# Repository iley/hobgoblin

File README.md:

# Hobgoblin: Z80-based single-board computer

## Specs

 - Z80 CPU running at 10MHz
 - 64 KiB RAM
 - 8 x 16 KiB ROM. ROM bank is selectable with a DIP switch
 - ROM can be paged out for CP/M compatibility
 - Built-in usb-to-serial adapter for convenience of use with modern computers
 - 2 RC2014-compatible extension slots.

## Memory map

```
 FFFF ┌─────────┐
      │         │
      │         │
      │         │
      │         │
      │   RAM   │
      │         │
      │         │
      │         │
 4000 ├─────────┤
      │         │
      │   ROM   │
      │         │
 0000 └─────────┘
```

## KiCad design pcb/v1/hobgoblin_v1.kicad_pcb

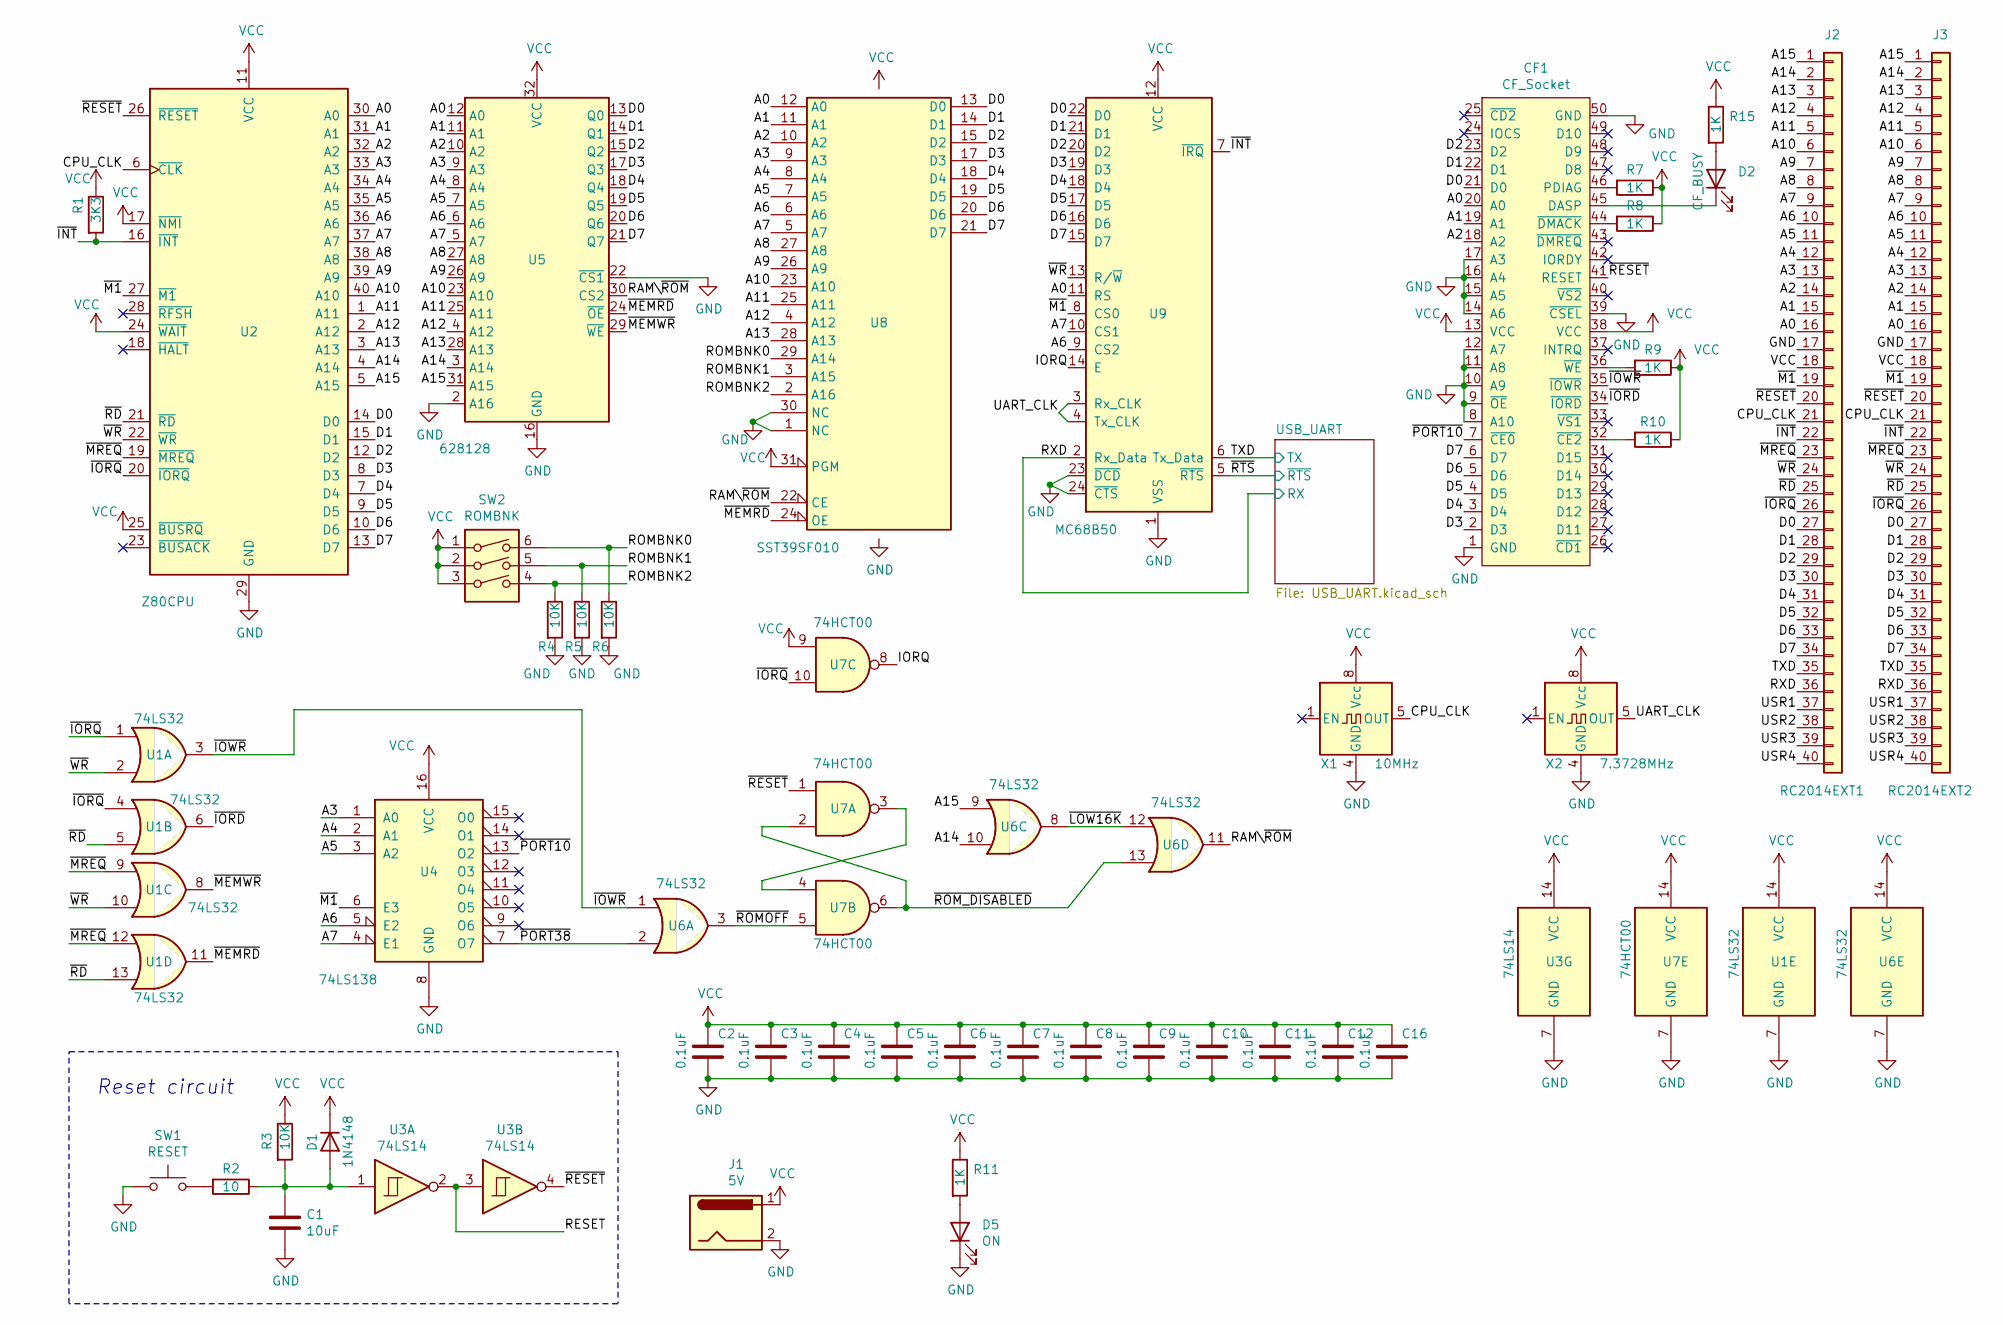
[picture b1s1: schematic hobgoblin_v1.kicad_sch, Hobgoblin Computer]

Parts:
C1: 10uF; CP_Radial_D4.0mm_P1.50mm
C2, C3, C4, C5, C6, C7, C8, C9, C10, C11, C12, C16: 0.1uF; C_Disc_D3.8mm_W2.6mm_P2.50mm
CF1: CF_Socket; CF-Card_3M_N7E507516PK20
D1: 1N4148; D_DO-35_SOD27_P7.62mm_Horizontal
D2: CF_BUSY; LED_D3.0mm
D5: ON; LED_D3.0mm
J1: 5V; BarrelJack_Horizontal
J2: RC2014EXT1; RC2014_Connector
J3: RC2014EXT2; RC2014_Connector
R1: 3K3; R_Axial_DIN0207_L6.3mm_D2.5mm_P10.16mm_Horizontal
R2: 10; R_Axial_DIN0207_L6.3mm_D2.5mm_P10.16mm_Horizontal
R3, R4, R5, R6: 10K; R_Axial_DIN0207_L6.3mm_D2.5mm_P10.16mm_Horizontal
R7, R8, R9, R10, R11, R15: 1K; R_Axial_DIN0207_L6.3mm_D2.5mm_P10.16mm_Horizontal
SW1: RESET; SW_PUSH_6mm
SW2: ROMBNK; SW_DIP_SPSTx03_Slide_6.7x9.18mm_W7.62mm_P2.54mm_LowProfile
U1, U6: 74LS32; DIP-14_W7.62mm_LongPads
U2: Z80CPU; DIP-40_W15.24mm_LongPads
U3: 74LS14; DIP-14_W7.62mm_LongPads
U4: 74LS138; DIP-16_W7.62mm_LongPads
U5: 628128; DIP-32_W15.24mm_LongPads
U7: 74HCT00; DIP-14_W7.62mm_LongPads
U8: SST39SF010; DIP-32_W15.24mm_LongPads
U9: MC68B50; DIP-24_W15.24mm_LongPads
X1: 10MHz; Oscillator_DIP-8
X2: 7.3728MHz; Oscillator_DIP-8

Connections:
/A0: CF1.20 (A0), J2.16, J3.16, U2.30 (A0), U5.12 (A0), U8.12 (A0), U9.11 (RS)
/A1: CF1.19 (A1), J2.15, J3.15, U2.31 (A1), U5.11 (A1), U8.11 (A1)
/A2: CF1.18 (A2), J2.14, J3.14, U2.32 (A2), U5.10 (A2), U8.10 (A2)
/A3: J2.13, J3.13, U2.33 (A3), U4.1 (A0), U5.9 (A3), U8.9 (A3)
/A4: J2.12, J3.12, U2.34 (A4), U4.2 (A1), U5.8 (A4), U8.8 (A4)
/A5: J2.11, J3.11, U2.35 (A5), U4.3 (A2), U5.7 (A5), U8.7 (A5)
/A6: J2.10, J3.10, U2.36 (A6), U4.5 (E2), U5.6 (A6), U8.6 (A6), U9.9 (CS2)
/A7: J2.9, J3.9, U2.37 (A7), U4.4 (E1), U5.5 (A7), U8.5 (A7), U9.10 (CS1)
/A8: J2.8, J3.8, U2.38 (A8), U5.27 (A8), U8.27 (A8)
/A9: J2.7, J3.7, U2.39 (A9), U5.26 (A9), U8.26 (A9)
/A10: J2.6, J3.6, U2.40 (A10), U5.23 (A10), U8.23 (A10)
/A11: J2.5, J3.5, U2.1 (A11), U5.25 (A11), U8.25 (A11)
/A12: J2.4, J3.4, U2.2 (A12), U5.4 (A12), U8.4 (A12)
/A13: J2.3, J3.3, U2.3 (A13), U5.28 (A13), U8.28 (A13)
/A14: J2.2, J3.2, U2.4 (A14), U5.3 (A14), U6.10
/A15: J2.1, J3.1, U2.5 (A15), U5.31 (A15), U6.9
/CPU_CLK: J2.21, J3.21, U2.6 (~CLK), X1.5 (OUT)
/D0: CF1.21 (D0), J2.27, J3.27, U2.14 (D0), U5.13 (Q0), U8.13 (D0), U9.22 (D0)
/D1: CF1.22 (D1), J2.28, J3.28, U2.15 (D1), U5.14 (Q1), U8.14 (D1), U9.21 (D1)
/D2: CF1.23 (D2), J2.29, J3.29, U2.12 (D2), U5.15 (Q2), U8.15 (D2), U9.20 (D2)
/D3: CF1.2 (D3), J2.30, J3.30, U2.8 (D3), U5.17 (Q3), U8.17 (D3), U9.19 (D3)
/D4: CF1.3 (D4), J2.31, J3.31, U2.7 (D4), U5.18 (Q4), U8.18 (D4), U9.18 (D4)
/D5: CF1.4 (D5), J2.32, J3.32, U2.9 (D5), U5.19 (Q5), U8.19 (D5), U9.17 (D5)
/D6: CF1.5 (D6), J2.33, J3.33, U2.10 (D6), U5.20 (Q6), U8.20 (D6), U9.16 (D6)
/D7: CF1.6 (D7), J2.34, J3.34, U2.13 (D7), U5.21 (Q7), U8.21 (D7), U9.15 (D7)
/IORQ: U7.8, U9.14 (E)
/RAM\~ROM: U5.30 (CS2), U6.11, U8.22 (CE)
/RESET: U3.2, U3.3
/ROMBNK0: R6.1, SW2.6, U8.29 (A14)
/ROMBNK1: R5.1, SW2.5, U8.3 (A15)
/ROMBNK2: R4.1, SW2.4, U8.2 (A16)
/RXD: J2.36, J3.36, U9.2 (Rx_Data); also elsewhere on the board
/TXD: J2.35, J3.35, U9.6 (Tx_Data); also elsewhere on the board
/UART_CLK: U9.3 (Rx_CLK), U9.4 (Tx_CLK), X2.5 (OUT)
/USR1: J2.37, J3.37
/USR2: J2.38, J3.38
/USR3: J2.39, J3.39
/USR4: J2.40, J3.40
/~INT: J2.22, J3.22, R1.2, U2.16 (~INT), U9.7 (~IRQ)
/~IORD: CF1.34 (~IORD), U1.6
/~IORQ: J2.26, J3.26, U1.1, U1.4, U2.20 (~IORQ), U7.10
/~IOWR: CF1.35 (~IOWR), U1.3, U6.1
/~LOW16K: U6.8, U6.12
/~M1: J2.19, J3.19, U2.27 (~M1), U4.6 (E3), U9.8 (CS0)
/~MEMRD: U1.11, U5.24 (~OE), U8.24 (OE)
/~MEMWR: U1.8, U5.29 (~WE)
/~MREQ: J2.23, J3.23, U1.9, U1.12, U2.19 (~MREQ)
/~PORT10: CF1.7 (~CE0), U4.13 (O2)
/~PORT38: U4.7 (O7), U6.2
/~RD: J2.25, J3.25, U1.5, U1.13, U2.21 (~RD)
/~RESET: CF1.41 (RESET), J2.20, J3.20, U2.26 (~RESET), U3.4, U7.1
/~ROMOFF: U6.3, U7.5
/~ROM_DISABLED: U6.13, U7.2, U7.6
/~RTS: U9.5 (~RTS); also elsewhere on the board
/~WR: J2.24, J3.24, U1.2, U1.10, U2.22 (~WR), U9.13 (R/~W)
GND: C1.2, C2.2, C3.2, C4.2, C5.2, C6.2, C7.2, C8.2, C9.2, C10.2, C11.2, C12.2, C16.2, CF1.1 (GND), CF1.8 (A10), CF1.9 (~OE), CF1.10 (A9), CF1.11 (A8), CF1.12 (A7), CF1.14 (A6), CF1.15 (A5), CF1.16 (A4), CF1.17 (A3), CF1.39 (~CSEL), CF1.50 (GND), D5.1 (K), J1.2, J2.17, J3.17, R4.2, R5.2, R6.2, SW1.1, U1.7 (GND), U2.29 (GND), U3.7 (GND), U4.8 (GND), U5.2 (A16), U5.16 (GND), U5.22 (~CS1), U6.7 (GND), U7.7 (GND), U8.1 (NC), U8.16 (GND), U8.30 (NC), U9.1 (VSS), U9.23 (~DCD), U9.24 (~CTS), X1.4 (GND), X2.4 (GND); also elsewhere on the board
unnamed: C1.1, D1.2 (A), R2.1, R3.2, U3.1
unnamed: CF1.32 (~CE2), R10.2
unnamed: CF1.36 (~WE), R9.2
unnamed: CF1.44 (~DMACK), R8.2
unnamed: CF1.45 (DASP), D2.1 (K)
unnamed: CF1.46 (PDIAG), R7.2
unnamed: D2.2 (A), R15.2
unnamed: D5.2 (A), R11.2
unnamed: R2.2, SW1.2
unnamed: U7.3, U7.4
VCC: C2.1, C3.1, C4.1, C5.1, C6.1, C7.1, C8.1, C9.1, C10.1, C11.1, C12.1, C16.1, CF1.13 (VCC), CF1.38 (VCC), D1.1 (K), J1.1, J2.18, J3.18, R1.1, R3.1, R7.1, R8.1, R9.1, R10.1, R11.1, R15.1, SW2.1, SW2.2, SW2.3, U1.14 (VCC), U2.11 (VCC), U2.17 (~NMI), U2.24 (~WAIT), U2.25 (~BUSRQ), U3.14 (VCC), U4.16 (VCC), U5.32 (VCC), U6.14 (VCC), U7.9, U7.14 (VCC), U8.31 (PGM), U8.32 (VCC), U9.12 (VCC), X1.8 (Vcc), X2.8 (Vcc); also elsewhere on the board

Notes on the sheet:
Reset circuit

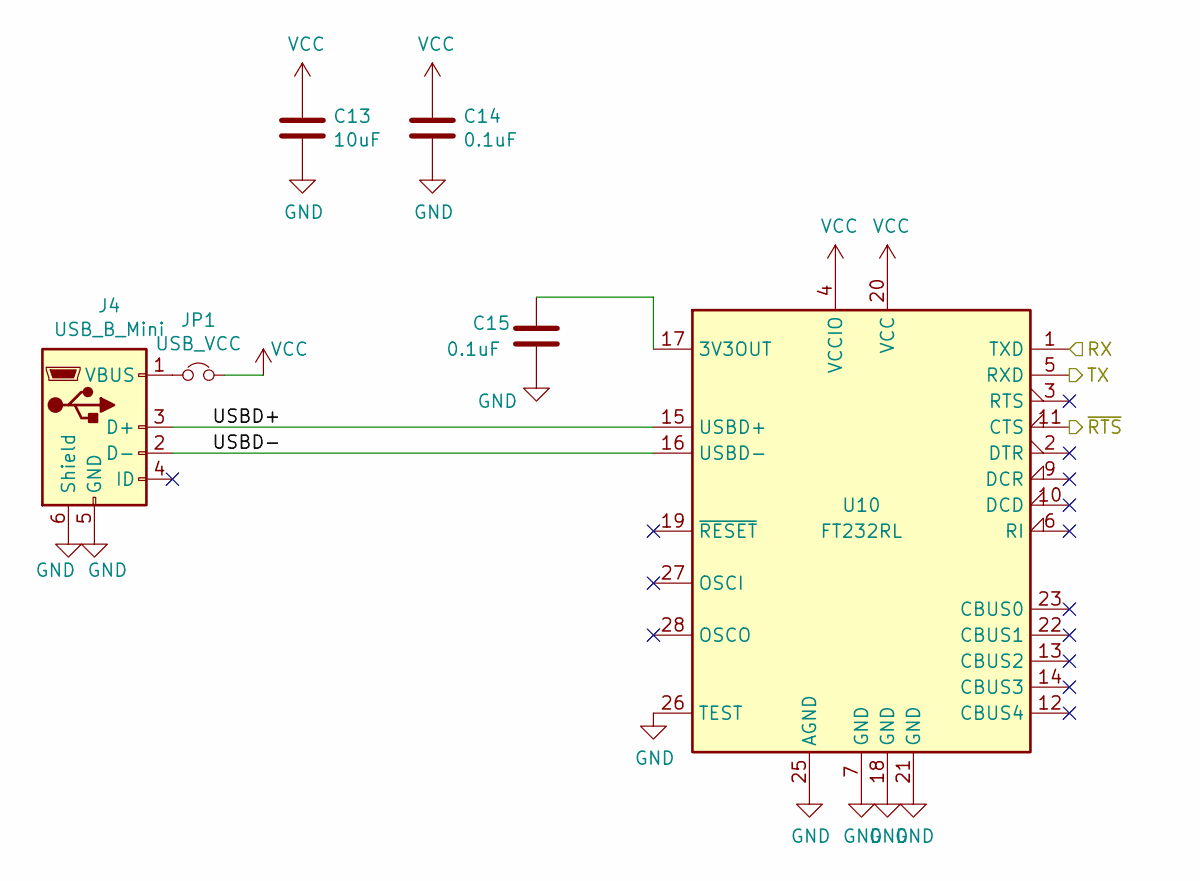
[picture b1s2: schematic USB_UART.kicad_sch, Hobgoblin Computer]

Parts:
C13: 10uF; CP_Radial_D4.0mm_P1.50mm
C14, C15: 0.1uF; C_Disc_D3.8mm_W2.6mm_P2.50mm
J4: USB_B_Mini; USB_Mini-B_Lumberg_2486_01_Horizontal
JP1: USB_VCC; PinHeader_1x02_P2.54mm_Vertical
U10: FT232RL; SSOP-28_5.3x10.2mm_P0.65mm

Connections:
/RXD: U10.1 (TXD); also elsewhere on the board
/TXD: U10.5 (RXD); also elsewhere on the board
/USB_UART/USBD+: J4.3 (D+), U10.15 (USBD+)
/USB_UART/USBD-: J4.2 (D-), U10.16 (USBD-)
/~RTS: U10.11 (CTS); also elsewhere on the board
GND: C13.2, C14.2, C15.1, J4.5 (GND), J4.6 (Shield), U10.7 (GND), U10.18 (GND), U10.21 (GND), U10.25 (AGND), U10.26 (TEST); also elsewhere on the board
unnamed: C15.2, U10.17 (3V3OUT)
unnamed: J4.1 (VBUS), JP1.1
VCC: C13.1, C14.1, JP1.2, U10.4 (VCCIO), U10.20 (VCC); also elsewhere on the board

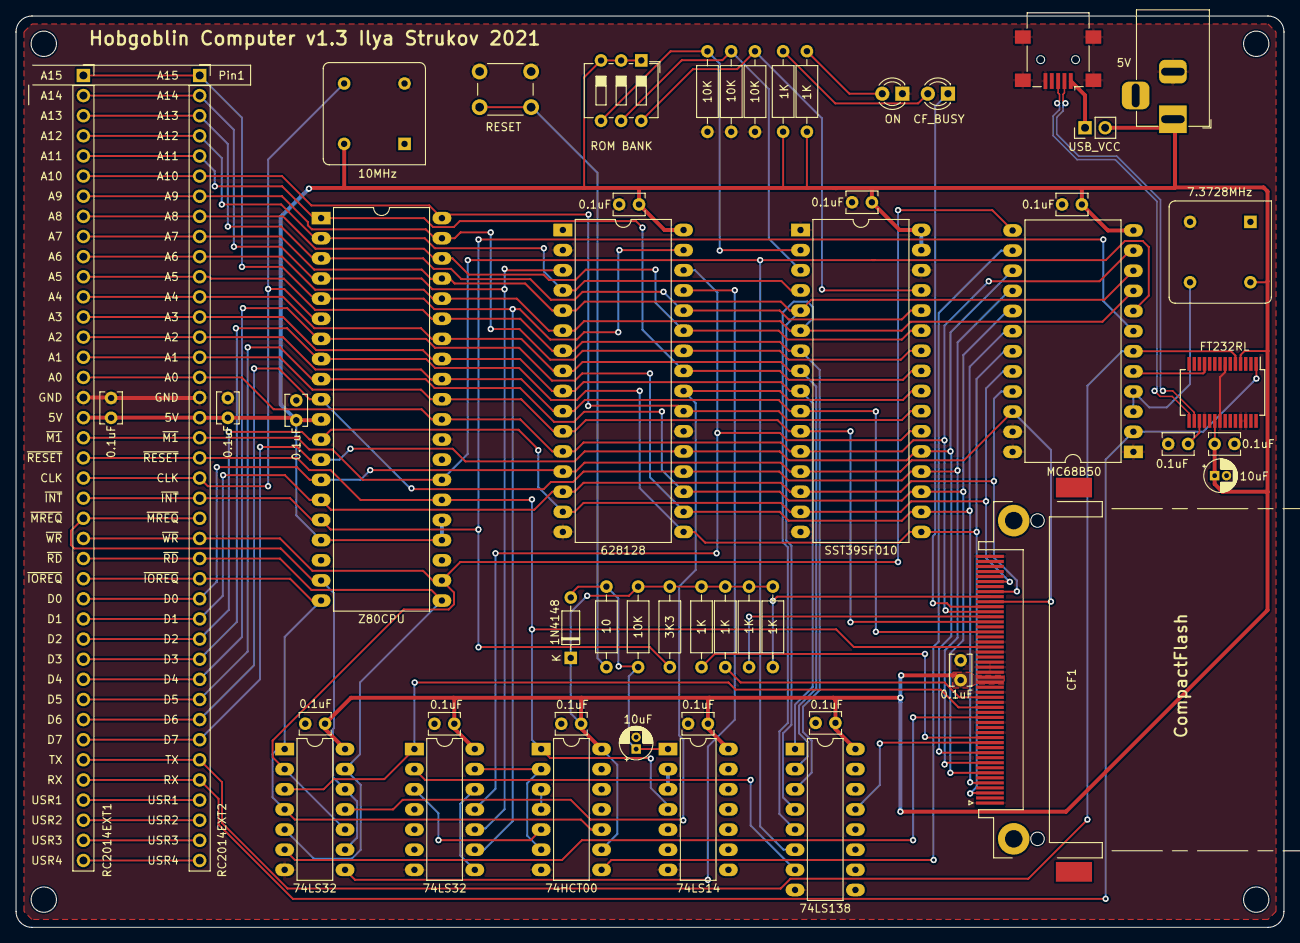
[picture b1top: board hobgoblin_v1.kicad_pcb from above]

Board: 2 copper layers, 160.0 x 115.0 mm, 51 parts (0 on the bottom side), 71 nets.

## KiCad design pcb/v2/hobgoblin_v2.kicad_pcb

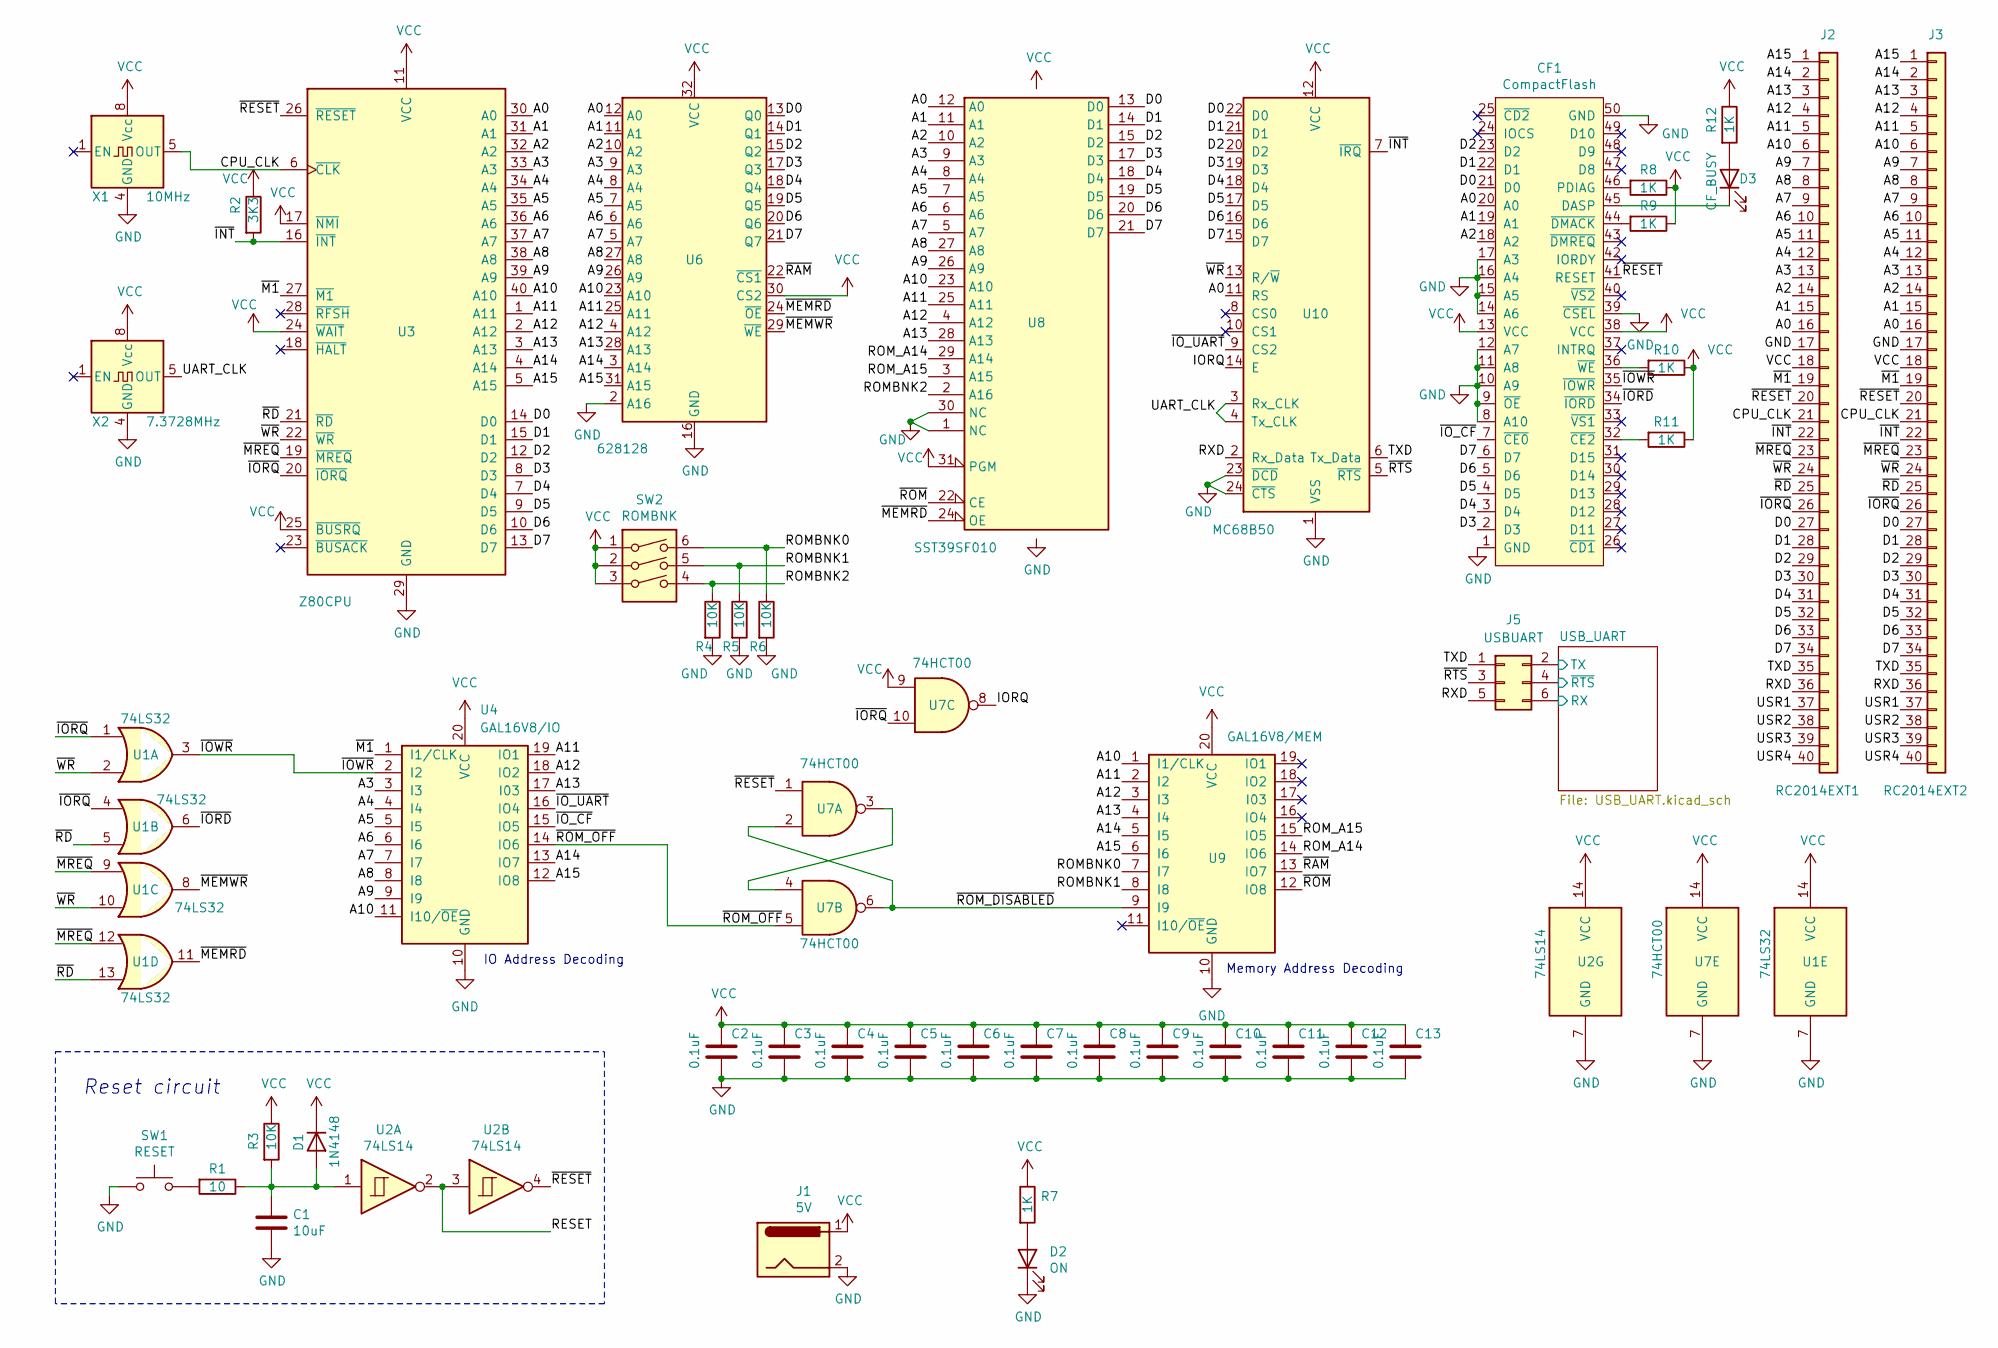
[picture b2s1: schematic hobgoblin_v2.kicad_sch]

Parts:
C1: 10uF; CP_Radial_D4.0mm_P1.50mm
C2, C3, C4, C5, C6, C7, C8, C9, C10, C11, C12, C13: 0.1uF; C_Disc_D3.8mm_W2.6mm_P2.50mm
CF1: CompactFlash; CF-Card_3M_N7E507516PK20
D1: 1N4148; D_DO-35_SOD27_P7.62mm_Horizontal
D2: ON; LED_D3.0mm
D3: CF_BUSY; LED_D3.0mm
J1: 5V; BarrelJack_Horizontal
J2: RC2014EXT1; RC2014_Connector
J3: RC2014EXT2; RC2014_Connector
J5: USBUART; PinHeader_2x03_P2.54mm_Vertical
R1: 10; R_Axial_DIN0207_L6.3mm_D2.5mm_P10.16mm_Horizontal
R2: 3K3; R_Axial_DIN0207_L6.3mm_D2.5mm_P10.16mm_Horizontal
R3, R4, R5, R6: 10K; R_Axial_DIN0207_L6.3mm_D2.5mm_P10.16mm_Horizontal
R7, R8, R9, R10, R11, R12: 1K; R_Axial_DIN0207_L6.3mm_D2.5mm_P10.16mm_Horizontal
SW1: RESET; SW_PUSH_6mm
SW2: ROMBNK; SW_DIP_SPSTx03_Slide_6.7x9.18mm_W7.62mm_P2.54mm_LowProfile
U1: 74LS32; DIP-14_W7.62mm_LongPads
U2: 74LS14; DIP-14_W7.62mm_LongPads
U3: Z80CPU; DIP-40_W15.24mm_Socket_LongPads
U4: GAL16V8/IO; DIP-20_W7.62mm_Socket_LongPads
U6: 628128; DIP-32_W15.24mm_LongPads
U7: 74HCT00; DIP-14_W7.62mm_LongPads
U8: SST39SF010; DIP-32_W15.24mm_Socket_LongPads
U9: GAL16V8/MEM; DIP-20_W7.62mm_Socket_LongPads
U10: MC68B50; DIP-24_W15.24mm_Socket_LongPads
X1: 10MHz; Oscillator_DIP-8
X2: 7.3728MHz; Oscillator_DIP-8

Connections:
/A0: CF1.20 (A0), J2.16, J3.16, U3.30 (A0), U6.12 (A0), U8.12 (A0), U10.11 (RS)
/A1: CF1.19 (A1), J2.15, J3.15, U3.31 (A1), U6.11 (A1), U8.11 (A1)
/A2: CF1.18 (A2), J2.14, J3.14, U3.32 (A2), U6.10 (A2), U8.10 (A2)
/A3: J2.13, J3.13, U3.33 (A3), U4.3 (I3), U6.9 (A3), U8.9 (A3)
/A4: J2.12, J3.12, U3.34 (A4), U4.4 (I4), U6.8 (A4), U8.8 (A4)
/A5: J2.11, J3.11, U3.35 (A5), U4.5 (I5), U6.7 (A5), U8.7 (A5)
/A6: J2.10, J3.10, U3.36 (A6), U4.6 (I6), U6.6 (A6), U8.6 (A6)
/A7: J2.9, J3.9, U3.37 (A7), U4.7 (I7), U6.5 (A7), U8.5 (A7)
/A8: J2.8, J3.8, U3.38 (A8), U4.8 (I8), U6.27 (A8), U8.27 (A8)
/A9: J2.7, J3.7, U3.39 (A9), U4.9 (I9), U6.26 (A9), U8.26 (A9)
/A10: J2.6, J3.6, U3.40 (A10), U4.11 (I10/~OE), U6.23 (A10), U8.23 (A10), U9.1 (I1/CLK)
/A11: J2.5, J3.5, U3.1 (A11), U4.19 (IO1), U6.25 (A11), U8.25 (A11), U9.2 (I2)
/A12: J2.4, J3.4, U3.2 (A12), U4.18 (IO2), U6.4 (A12), U8.4 (A12), U9.3 (I3)
/A13: J2.3, J3.3, U3.3 (A13), U4.17 (I03), U6.28 (A13), U8.28 (A13), U9.4 (I4)
/A14: J2.2, J3.2, U3.4 (A14), U4.13 (IO7), U6.3 (A14), U9.5 (I5)
/A15: J2.1, J3.1, U3.5 (A15), U4.12 (IO8), U6.31 (A15), U9.6 (I6)
/CPU_CLK: J2.21, J3.21, U3.6 (~CLK), X1.5 (OUT)
/D0: CF1.21 (D0), J2.27, J3.27, U3.14 (D0), U6.13 (Q0), U8.13 (D0), U10.22 (D0)
/D1: CF1.22 (D1), J2.28, J3.28, U3.15 (D1), U6.14 (Q1), U8.14 (D1), U10.21 (D1)
/D2: CF1.23 (D2), J2.29, J3.29, U3.12 (D2), U6.15 (Q2), U8.15 (D2), U10.20 (D2)
/D3: CF1.2 (D3), J2.30, J3.30, U3.8 (D3), U6.17 (Q3), U8.17 (D3), U10.19 (D3)
/D4: CF1.3 (D4), J2.31, J3.31, U3.7 (D4), U6.18 (Q4), U8.18 (D4), U10.18 (D4)
/D5: CF1.4 (D5), J2.32, J3.32, U3.9 (D5), U6.19 (Q5), U8.19 (D5), U10.17 (D5)
/D6: CF1.5 (D6), J2.33, J3.33, U3.10 (D6), U6.20 (Q6), U8.20 (D6), U10.16 (D6)
/D7: CF1.6 (D7), J2.34, J3.34, U3.13 (D7), U6.21 (Q7), U8.21 (D7), U10.15 (D7)
/IORQ: U7.8, U10.14 (E)
/RESET: U2.2, U2.3
/ROMBNK0: R6.1, SW2.6, U9.7 (I7)
/ROMBNK1: R5.1, SW2.5, U9.8 (I8)
/ROMBNK2: R4.1, SW2.4, U8.2 (A16)
/ROM_A14: U8.29 (A14), U9.14 (IO6)
/ROM_A15: U8.3 (A15), U9.15 (IO5)
/RXD: J2.36, J3.36, J5.5, U10.2 (Rx_Data)
/TXD: J2.35, J3.35, J5.1, U10.6 (Tx_Data)
/UART_CLK: U10.3 (Rx_CLK), U10.4 (Tx_CLK), X2.5 (OUT)
/USB_UART/RX: J5.6; also elsewhere on the board
/USB_UART/TX: J5.2; also elsewhere on the board
/USB_UART/~RTS: J5.4; also elsewhere on the board
/USR1: J2.37, J3.37
/USR2: J2.38, J3.38
/USR3: J2.39, J3.39
/USR4: J2.40, J3.40
/~INT: J2.22, J3.22, R2.2, U3.16 (~INT), U10.7 (~IRQ)
/~IORD: CF1.34 (~IORD), U1.6
/~IORQ: J2.26, J3.26, U1.1, U1.4, U3.20 (~IORQ), U7.10
/~IOWR: CF1.35 (~IOWR), U1.3, U4.2 (I2)
/~IO_CF: CF1.7 (~CE0), U4.15 (IO5)
/~IO_UART: U4.16 (IO4), U10.9 (CS2)
/~M1: J2.19, J3.19, U3.27 (~M1), U4.1 (I1/CLK)
/~MEMRD: U1.11, U6.24 (~OE), U8.24 (OE)
/~MEMWR: U1.8, U6.29 (~WE)
/~MREQ: J2.23, J3.23, U1.9, U1.12, U3.19 (~MREQ)
/~RAM: U6.22 (~CS1), U9.13 (IO7)
/~RD: J2.25, J3.25, U1.5, U1.13, U3.21 (~RD)
/~RESET: CF1.41 (RESET), J2.20, J3.20, U2.4, U3.26 (~RESET), U7.1
/~ROM_DISABLED: U7.2, U7.6, U9.9 (I9)
/~ROM_OFF: U4.14 (IO6), U7.5
/~ROM: U8.22 (CE), U9.12 (IO8)
/~RTS: J5.3, U10.5 (~RTS)
/~WR: J2.24, J3.24, U1.2, U1.10, U3.22 (~WR), U10.13 (R/~W)
GND: C1.2, C2.2, C3.2, C4.2, C5.2, C6.2, C7.2, C8.2, C9.2, C10.2, C11.2, C12.2, C13.2, CF1.1 (GND), CF1.8 (A10), CF1.9 (~OE), CF1.10 (A9), CF1.11 (A8), CF1.12 (A7), CF1.14 (A6), CF1.15 (A5), CF1.16 (A4), CF1.17 (A3), CF1.39 (~CSEL), CF1.50 (GND), D2.1 (K), J1.2, J2.17, J3.17, R4.2, R5.2, R6.2, SW1.1, U1.7 (GND), U2.7 (GND), U3.29 (GND), U4.10 (GND), U6.2 (A16), U6.16 (GND), U7.7 (GND), U8.1 (NC), U8.16 (GND), U8.30 (NC), U9.10 (GND), U10.1 (VSS), U10.23 (~DCD), U10.24 (~CTS), X1.4 (GND), X2.4 (GND); also elsewhere on the board
unnamed: C1.1, D1.2 (A), R1.1, R3.2, U2.1
unnamed: CF1.32 (~CE2), R11.2
unnamed: CF1.36 (~WE), R10.2
unnamed: CF1.44 (~DMACK), R9.2
unnamed: CF1.45 (DASP), D3.1 (K)
unnamed: CF1.46 (PDIAG), R8.2
unnamed: D2.2 (A), R7.2
unnamed: D3.2 (A), R12.2
unnamed: R1.2, SW1.2
unnamed: U7.3, U7.4
VCC: C2.1, C3.1, C4.1, C5.1, C6.1, C7.1, C8.1, C9.1, C10.1, C11.1, C12.1, C13.1, CF1.13 (VCC), CF1.38 (VCC), D1.1 (K), J1.1, J2.18, J3.18, R2.1, R3.1, R7.1, R8.1, R9.1, R10.1, R11.1, R12.1, SW2.1, SW2.2, SW2.3, U1.14 (VCC), U2.14 (VCC), U3.11 (VCC), U3.17 (~NMI), U3.24 (~WAIT), U3.25 (~BUSRQ), U4.20 (VCC), U6.30 (CS2), U6.32 (VCC), U7.9, U7.14 (VCC), U8.31 (PGM), U8.32 (VCC), U9.20 (VCC), U10.12 (VCC), X1.8 (Vcc), X2.8 (Vcc); also elsewhere on the board

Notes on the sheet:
Reset circuit
IO Address Decoding
Memory Address Decoding

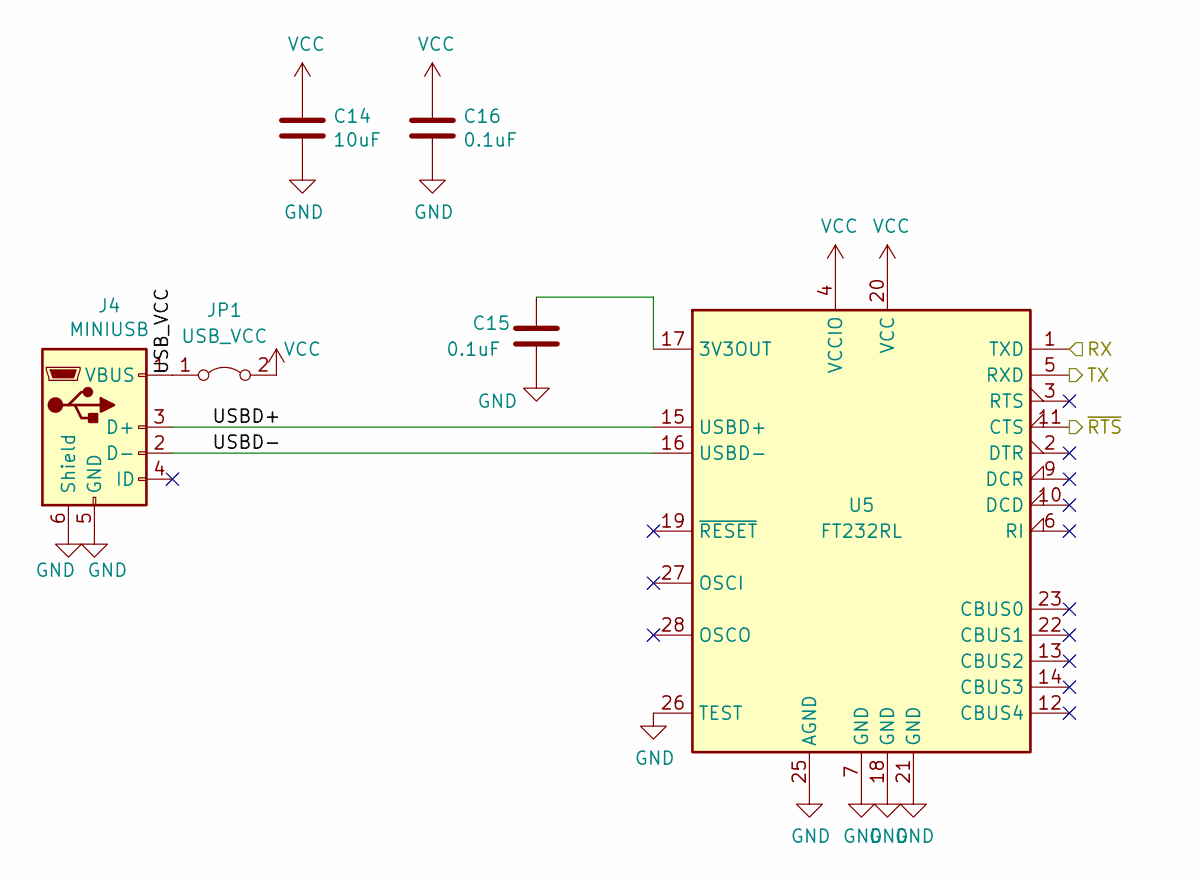
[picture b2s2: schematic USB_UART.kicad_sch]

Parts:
C14: 10uF; CP_Radial_D4.0mm_P1.50mm
C15, C16: 0.1uF; C_Disc_D3.8mm_W2.6mm_P2.50mm
J4: MINIUSB; USB_Mini-B_Lumberg_2486_01_Horizontal
JP1: USB_VCC; PinSocket_1x02_P2.54mm_Vertical
U5: FT232RL; SSOP-28_5.3x10.2mm_P0.65mm

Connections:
/USB_UART/RX: U5.1 (TXD); also elsewhere on the board
/USB_UART/TX: U5.5 (RXD); also elsewhere on the board
/USB_UART/USBD+: J4.3 (D+), U5.15 (USBD+)
/USB_UART/USBD-: J4.2 (D-), U5.16 (USBD-)
/USB_UART/USB_VCC: J4.1 (VBUS), JP1.1 (A)
/USB_UART/~RTS: U5.11 (CTS); also elsewhere on the board
GND: C14.2, C15.1, C16.2, J4.5 (GND), J4.6 (Shield), U5.7 (GND), U5.18 (GND), U5.21 (GND), U5.25 (AGND), U5.26 (TEST); also elsewhere on the board
unnamed: C15.2, U5.17 (3V3OUT)
VCC: C14.1, C16.1, JP1.2 (B), U5.4 (VCCIO), U5.20 (VCC); also elsewhere on the board

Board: 2 copper layers, 56 parts (0 on the bottom side), 76 nets, no tracks yet.

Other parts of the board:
H1: hole1; MountingHole_3.2mm_M3
H2: hole2; MountingHole_3.2mm_M3
H3: hole3; MountingHole_3.2mm_M3
H4: hole4; MountingHole_3.2mm_M3

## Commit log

2020-10-25 progress with the schematic
2020-11-03 Finish the schematic
2020-11-03 Place components on the PCB layout
2020-11-05 Finish PCB layout
2020-11-06 Add UART socket and other PCB improvements
2020-11-06 Add CF busy LED
2020-11-06 Flip the UART connector
2020-11-06 PCB: final touches
2020-11-08 Minor PCB changes
2020-12-24 Noop
2020-12-24 Fix the CF card slot footprint (v1.1.)
2021-01-01 Fix CF footprint pin numbering
2021-01-03 Reroute USB diff pair
2021-01-03 Save the schematic as PDF
2021-01-03 Add shell model
2021-01-23 Fix IOWR/IORD pins on CF socket
2021-01-23 Clean up routing
2021-01-23 Update the schematic PDF
2021-01-24 Add missing traces
2021-01-24 Final 1.3 routing improvements
2021-01-25 Cleanup
2021-08-23 Start implementing an emulator
2021-08-24 Start the emulator from scratch
2021-08-24 Start implementing an emulator in C++
2021-08-24 Implement ROM and loading data into memory
2021-08-29 Implement a bus device, start CPU
2021-08-29 Further progress on the emulator
    - Make CPU functional
    - Add NullDevice
    - Drop unnecessary const's
2021-08-31 Another CPU unit test
2021-09-09 Switch to Bazel
2021-09-09 Basic emulation loop
2021-09-09 Add Emulator class, multithreading
2021-09-14 Add MC6850 ACIA emulation (not working yet)
2021-12-15 Misc. emulator changes
2021-12-26 Convert PCB files to KiCAD v6
2021-12-27 Add readme
2021-12-27 README formatting
2021-12-27 Rename CF Card connector footprint to match the actual part
2021-12-28 Start v2 schematic
2021-12-29 Start using GALs in V2
2021-12-30 Draft component placement
2021-12-30 Realign components
2021-12-30 CF socket properties
2021-12-30 Tweak silkscreen
2021-12-30 Add ground fills
2021-12-31 In-progress PCB layout
2022-01-02 PCB layout in progress
2022-01-03 Made some progress in layout
2025-01-09 Update to latest KiCAD version
